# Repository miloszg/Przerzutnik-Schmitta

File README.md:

# Przerzutnik-Schmitta EAGLE 8.7.0
Rozbudowany generator akustyczny dla uzyskania prostokątnego sygnały wyjściowego

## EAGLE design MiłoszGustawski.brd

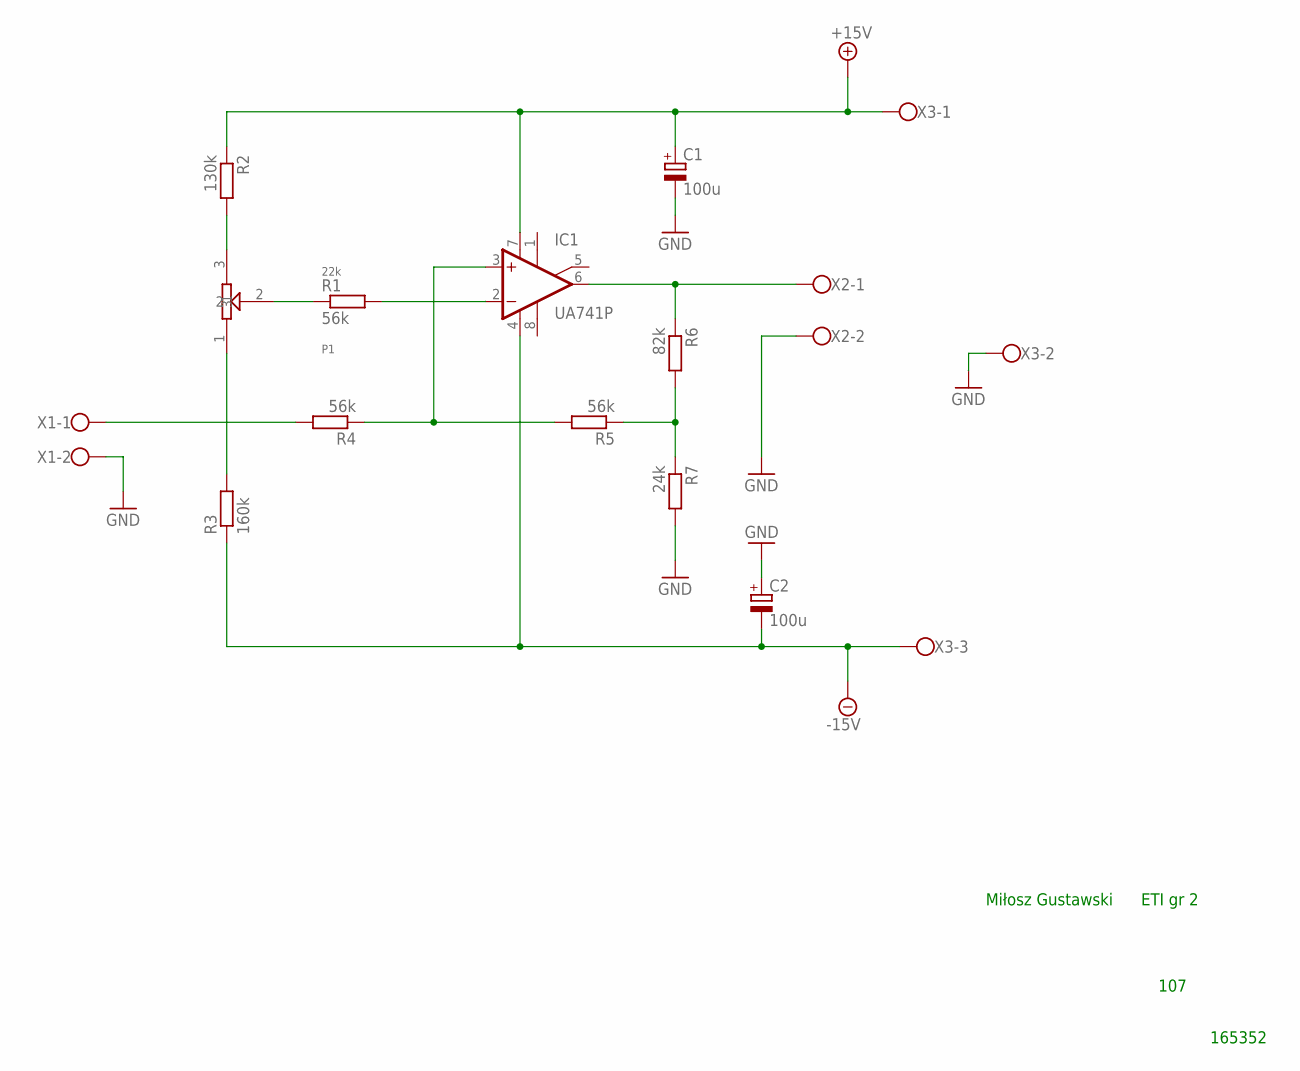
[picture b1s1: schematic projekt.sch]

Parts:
C1, C2: 100u; 140CLH-1014
IC1: UA741P; DIL08
P1: 22k; CN15.2
R1, R4, R5: 56k; 0207/10
R2: 130k; 0207/10
R3: 160k; 0207/10
R6: 82k; 0207/10
R7: 24k; 0207/10
X1, X2: W237-102
X3: W237-103

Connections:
+15V: C1.+, IC1.7 (V+), R2.1, X3.1
-15V: C2.-, IC1.4 (V-), R3.1, X3.3
GND: C1.-, C2.+, R7.2, X1.2, X2.2, X3.2
unnamed: R4.2, X1.1
unnamed: IC1.2 (-IN), R1.2
unnamed: P1.3, R2.2
unnamed: P1.1, R3.2
unnamed: P1.2, R1.1
unnamed: IC1.3 (+IN), R4.1, R5.2
unnamed: R5.1, R6.2, R7.1
unnamed: IC1.6 (OUT), R6.1, X2.1

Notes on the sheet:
Miłosz Gustawski
107
165352
ETI gr 2

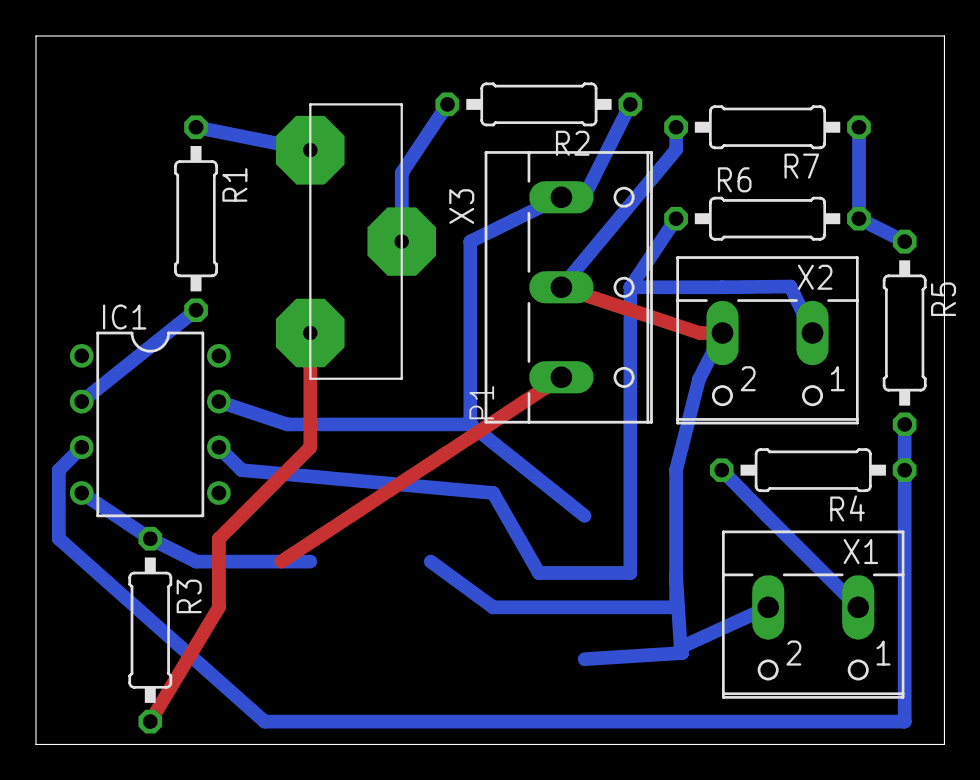
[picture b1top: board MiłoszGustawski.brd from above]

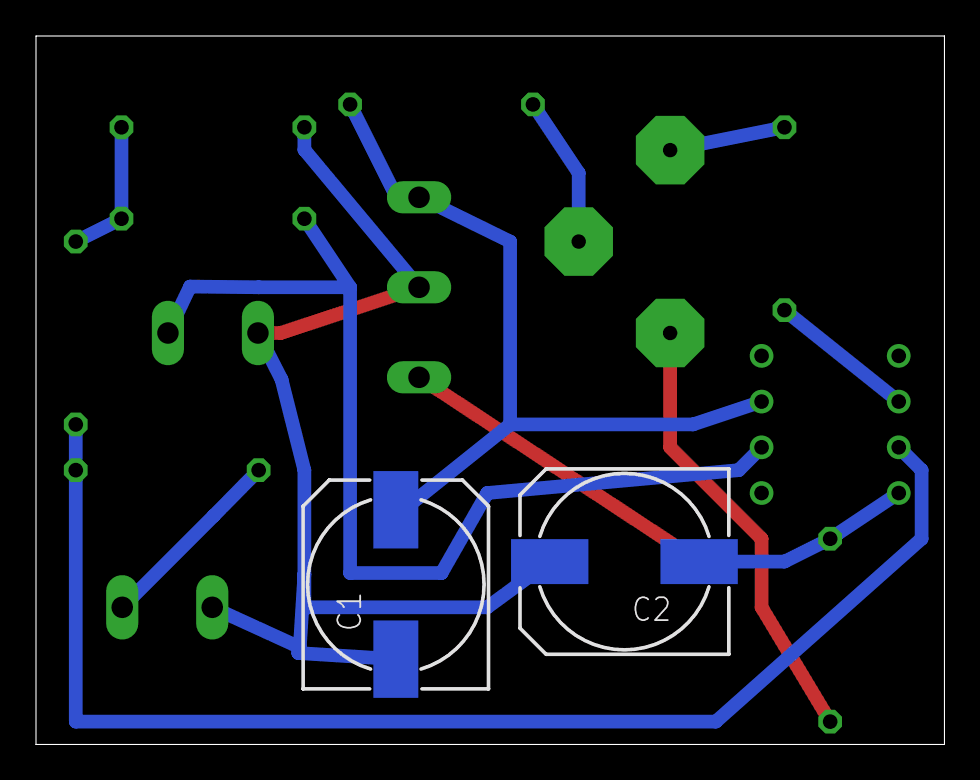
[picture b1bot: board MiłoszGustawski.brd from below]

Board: 2 copper layers, 50.5 x 39.4 mm, 14 parts (2 on the bottom side), 11 nets.
